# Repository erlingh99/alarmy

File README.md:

# Alarmy

A sunrise alarm system with a web interface and Raspberry Pi Pico W based light control. Wake up naturally with a simulated sunrise.

## Project Overview

This project consists of three main components:

- **Frontend**: React-based web interface for managing alarms
- **Backend**: FastAPI server for alarm storage and management 
- **Embedded**: Raspberry Pi Pico W controller for LED and buzzer control in 100% heapless Rust

## Quick Start

### Backend & Frontend

```bash
# Start the complete system using Docker
docker compose up -d --build
```

The web interface will be available at localhost port 80

### Pico W Setup

1. Flash the firmware following instructions in `/embedded/README.md`
2. Wire up a breadboard or use the PCB
3. Power up the device

## Development

See the individual component READMEs for detailed development instructions:

- [Frontend Documentation](frontend/README.md)
- [Backend Documentation](backend/README.md)
- [Embedded Documentation](embedded/README.md)

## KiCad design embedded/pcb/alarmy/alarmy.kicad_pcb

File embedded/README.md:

# Raspberry Pi Pico W Alarm Controller

This is the embedded component of the alarm project, implemented in Rust using the Embassy async runtime. It controls a PWM-capable LED strip and optional buzzer, fetching alarm schedules from the backend.

## Provisioning a device

The CYW43 WiFi chip blobs and the WiFi credentials are not part of the firmware binary. They are
flashed once per device at fixed addresses (see `memory_layout.toml`), so the firmware served
publicly for OTA contains no secrets. All scripts use picotool and need the Pico in BOOTSEL mode.

A new device, from `embedded/`:

```bash
uv run scripts/flash_blobs.py --no-reboot          # CYW43 blobs + credentials (prompts for SSID and password)
uv run scripts/flash_bootloader.py --no-reboot     # builds and flashes the bootloader
uv run scripts/flash_firmware.py                   # builds and flashes the firmware, then reboots
```

After that the firmware updates itself over OTA. Other useful variants:

```bash
uv run scripts/flash_blobs.py --only creds --ssid MyNetwork   # change network
uv run scripts/flash_blobs.py --only cyw43                    # chip blobs only
uv run scripts/flash_firmware.py --no-build                   # flash the existing release ELF
```

Without credentials the firmware boots but logs `No usable WiFi credentials in flash` over USB
serial every minute.

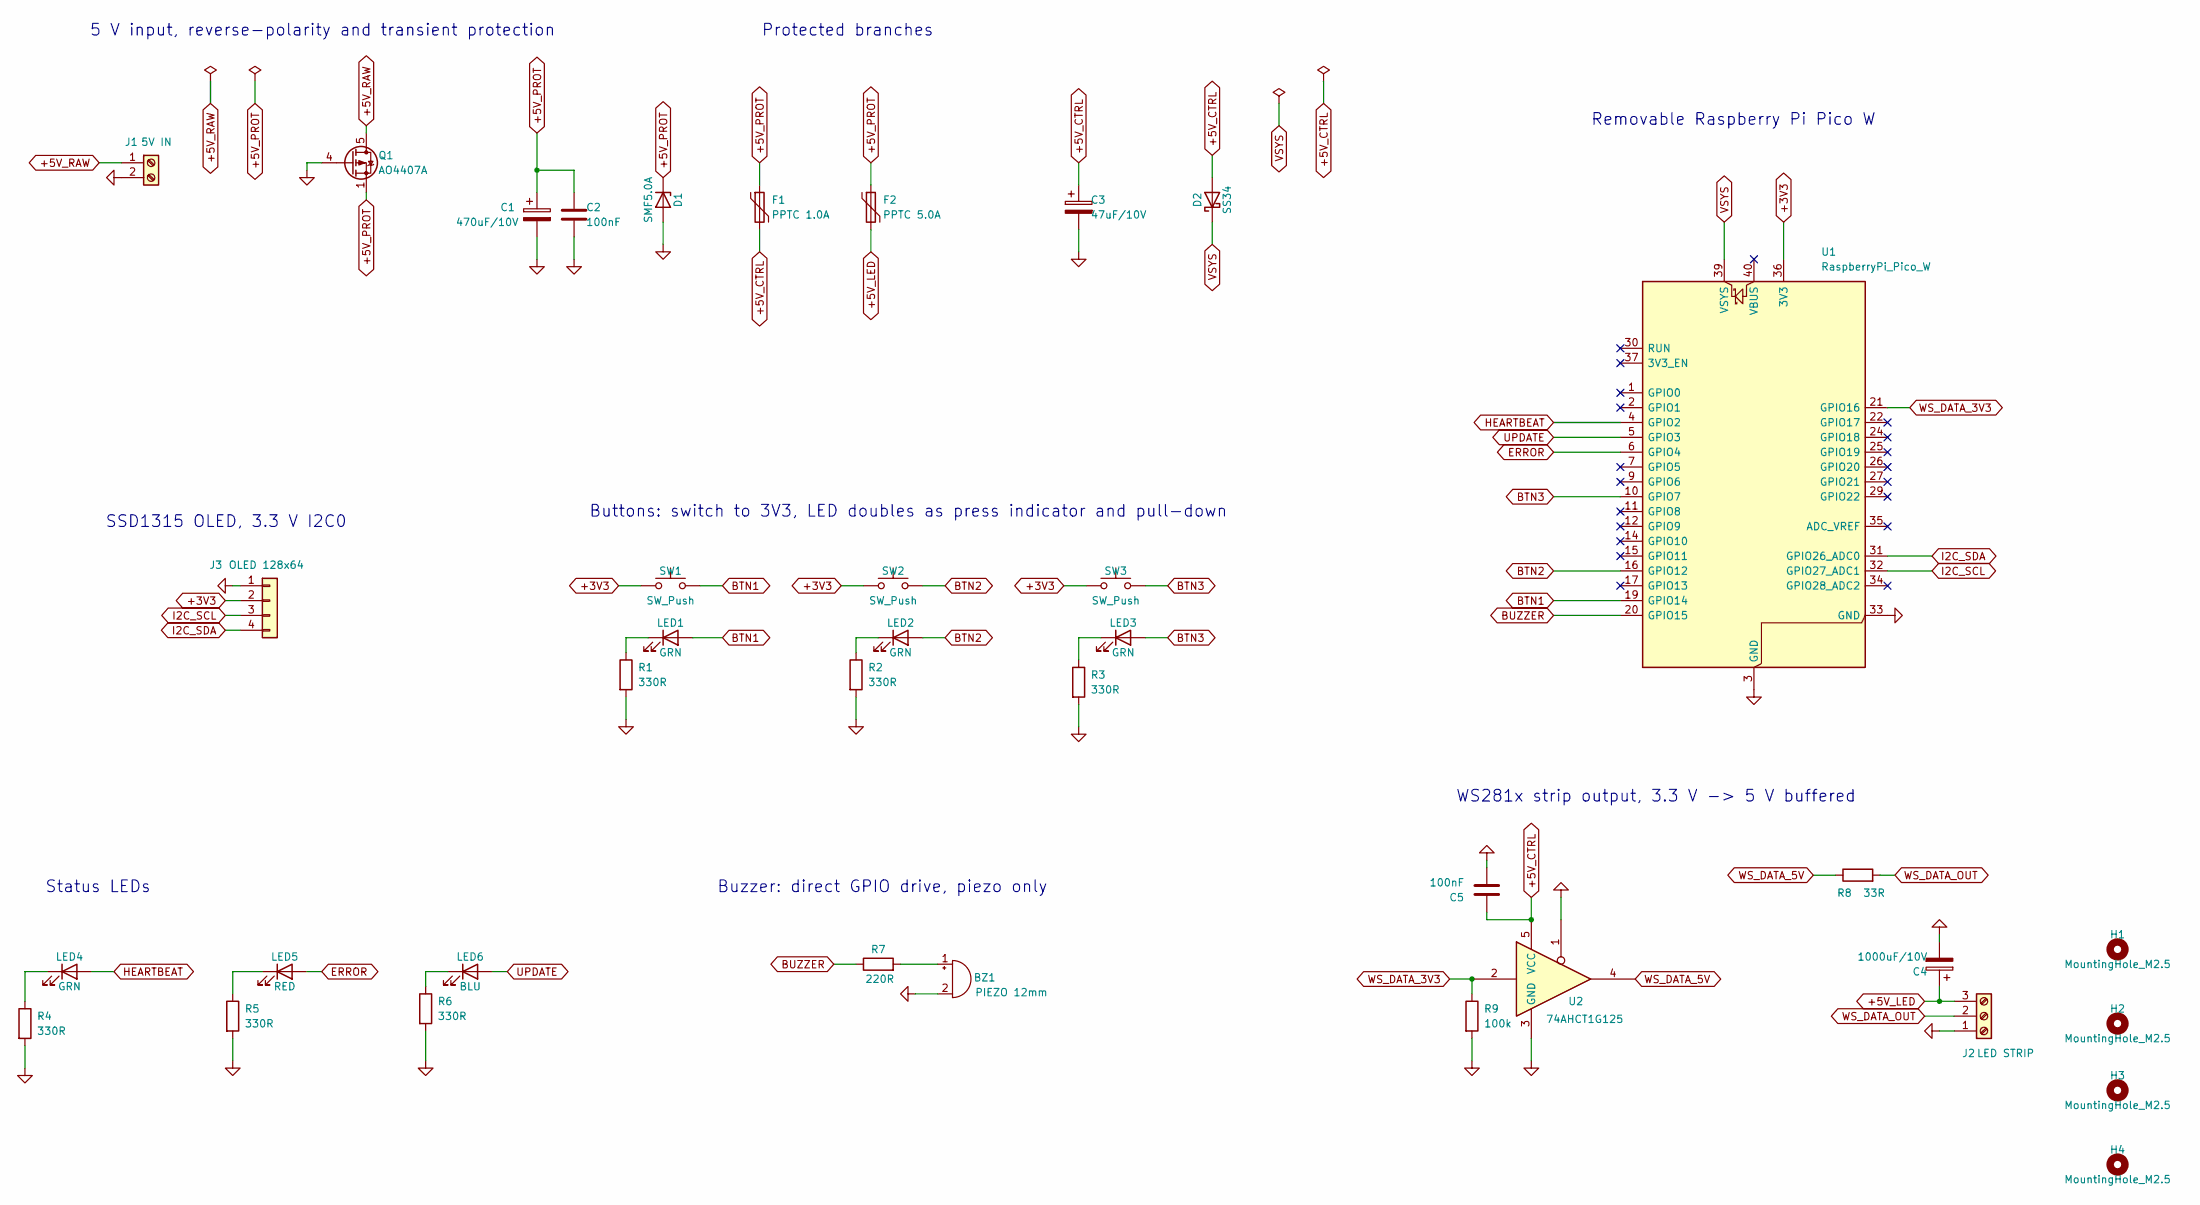
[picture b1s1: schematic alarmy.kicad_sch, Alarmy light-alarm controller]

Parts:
BZ1: PIEZO 12mm; Buzzer_12x9.5RM7.6
C1: 470uF/10V; CP_Radial_D8.0mm_P3.50mm
C2, C5: 100nF; C_Disc_D5.0mm_W2.5mm_P5.00mm
C3: 47uF/10V; CP_Radial_D5.0mm_P2.50mm
C4: 1000uF/10V; CP_Radial_D12.5mm_P5.00mm
D1: SMF5.0A; D_SMF; MPN SMF5.0A
D2: SS34; D_SMA; MPN SS34
F1: PPTC 1.0A; PPTC_Radial_P5.08mm; MPN MF-MSMF110-2
F2: PPTC 5.0A; PPTC_Radial_P10.0mm; MPN PTR030V0500-BK
H1, H2, H3, H4: MountingHole_M2.5; MountingHole_2.7mm_M2.5
J1: 5V IN; TerminalBlock_Phoenix_MKDS-1,5-2-5.08_1x02_P5.08mm_Horizont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; MPN Phoenix MKDS 1,5/2-5,08
J2: LED STRIP; TerminalBlock_Phoenix_MKDS-1,5-3-5.08_1x03_P5.08mm_Horizont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; MPN Phoenix MKDS 1,5/3-5,08
J3: OLED 128x64; OLED_SSD1315_0.96in_I2C
LED1, LED2, LED3, LED4: GRN; LED_D5.0mm
LED5: RED; LED_D5.0mm
LED6: BLU; LED_D5.0mm
Q1: AO4407A; SOIC-8_3.9x4.9mm_P1.27mm; MPN AO4407A
R1, R2, R3, R4, R5, R6: 330R; R_Axial_DIN0207_L6.3mm_D2.5mm_P7.62mm_Horizontal
R7: 220R; R_Axial_DIN0207_L6.3mm_D2.5mm_P7.62mm_Horizontal
R8: 33R; R_Axial_DIN0207_L6.3mm_D2.5mm_P7.62mm_Horizontal
R9: 100k; R_Axial_DIN0207_L6.3mm_D2.5mm_P7.62mm_Horizontal
SW1, SW2, SW3: SW_Push; SW_PUSH_6mm
U1: RaspberryPi_Pico_W; RaspberryPi_Pico_Common_THT
U2: 74AHCT1G125; SOT-23-5; MPN SN74AHCT1G125DBVR

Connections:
+3V3: J3.2, SW1.1, SW2.1, SW3.1, U1.36 (3V3)
+5V_CTRL: C3.1, C5.1, D2.2 (A), F1.2, U2.5 (VCC)
+5V_LED: C4.1, F2.2, J2.3
+5V_PROT: C1.1, C2.1, D1.1 (K), F1.1, F2.1, Q1.1 (S), Q1.2 (S), Q1.3 (S)
+5V_RAW: J1.1, Q1.5 (D), Q1.6 (D), Q1.7 (D), Q1.8 (D)
BTN1: LED1.2 (A), SW1.2, U1.19 (GPIO14)
BTN2: LED2.2 (A), SW2.2, U1.16 (GPIO12)
BTN3: LED3.2 (A), SW3.2, U1.10 (GPIO7)
BUZZER: R7.1, U1.20 (GPIO15)
ERROR: LED5.2 (A), U1.6 (GPIO4)
GND: BZ1.2 (-), C1.2, C2.2, C3.2, C4.2, C5.2, D1.2 (A), J1.2, J2.1, J3.1, Q1.4 (G), R1.2, R2.2, R3.2, R4.2, R5.2, R6.2, R9.2, U1.3 (GND), U1.8 (GND), U1.13 (GND), U1.18 (GND), U1.23 (GND), U1.28 (GND), U1.33 (GND), U1.38 (GND), U2.1, U2.3 (GND)
HEARTBEAT: LED4.2 (A), U1.4 (GPIO2)
I2C_SCL: J3.3, U1.32 (GPIO27_ADC1)
I2C_SDA: J3.4, U1.31 (GPIO26_ADC0)
unnamed: BZ1.1 (+), R7.2
unnamed: LED1.1 (K), R1.1
unnamed: LED2.1 (K), R2.1
unnamed: LED3.1 (K), R3.1
unnamed: LED4.1 (K), R4.1
unnamed: LED5.1 (K), R5.1
unnamed: LED6.1 (K), R6.1
UPDATE: LED6.2 (A), U1.5 (GPIO3)
VSYS: D2.1 (K), U1.39 (VSYS)
WS_DATA_3V3: R9.1, U1.21 (GPIO16), U2.2
WS_DATA_5V: R8.1, U2.4
WS_DATA_OUT: J2.2, R8.2

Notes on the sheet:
Protected branches
Buzzer: direct GPIO drive, piezo only
5 V input, reverse-polarity and transient protection
WS281x strip output, 3.3 V -> 5 V buffered
SSD1315 OLED, 3.3 V I2C0
Status LEDs
Buttons: switch to 3V3, LED doubles as press indicator and pull-down
Removable Raspberry Pi Pico W

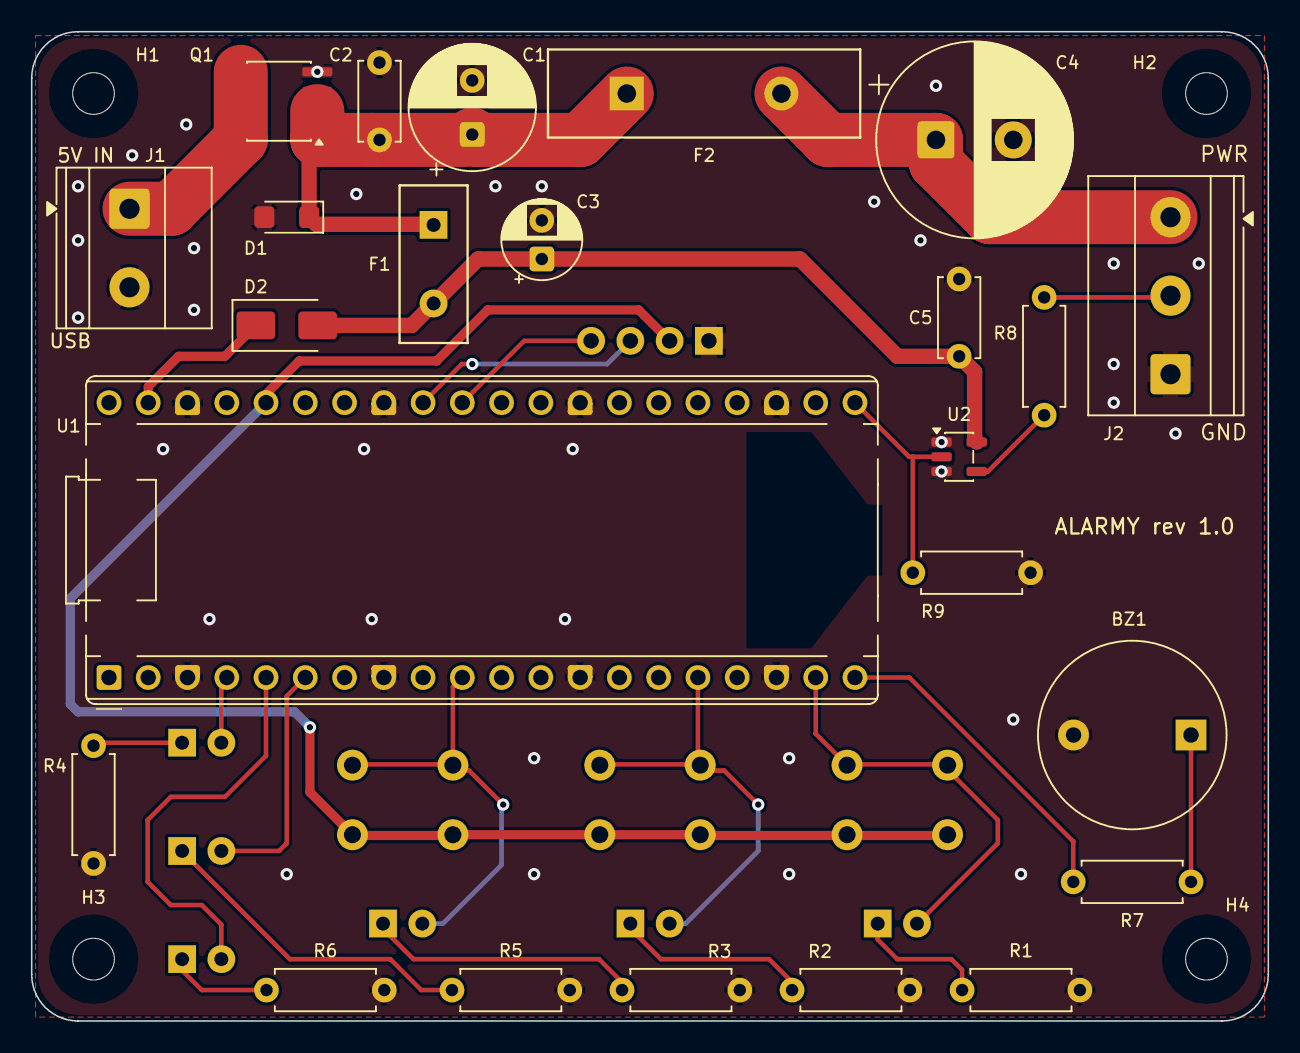
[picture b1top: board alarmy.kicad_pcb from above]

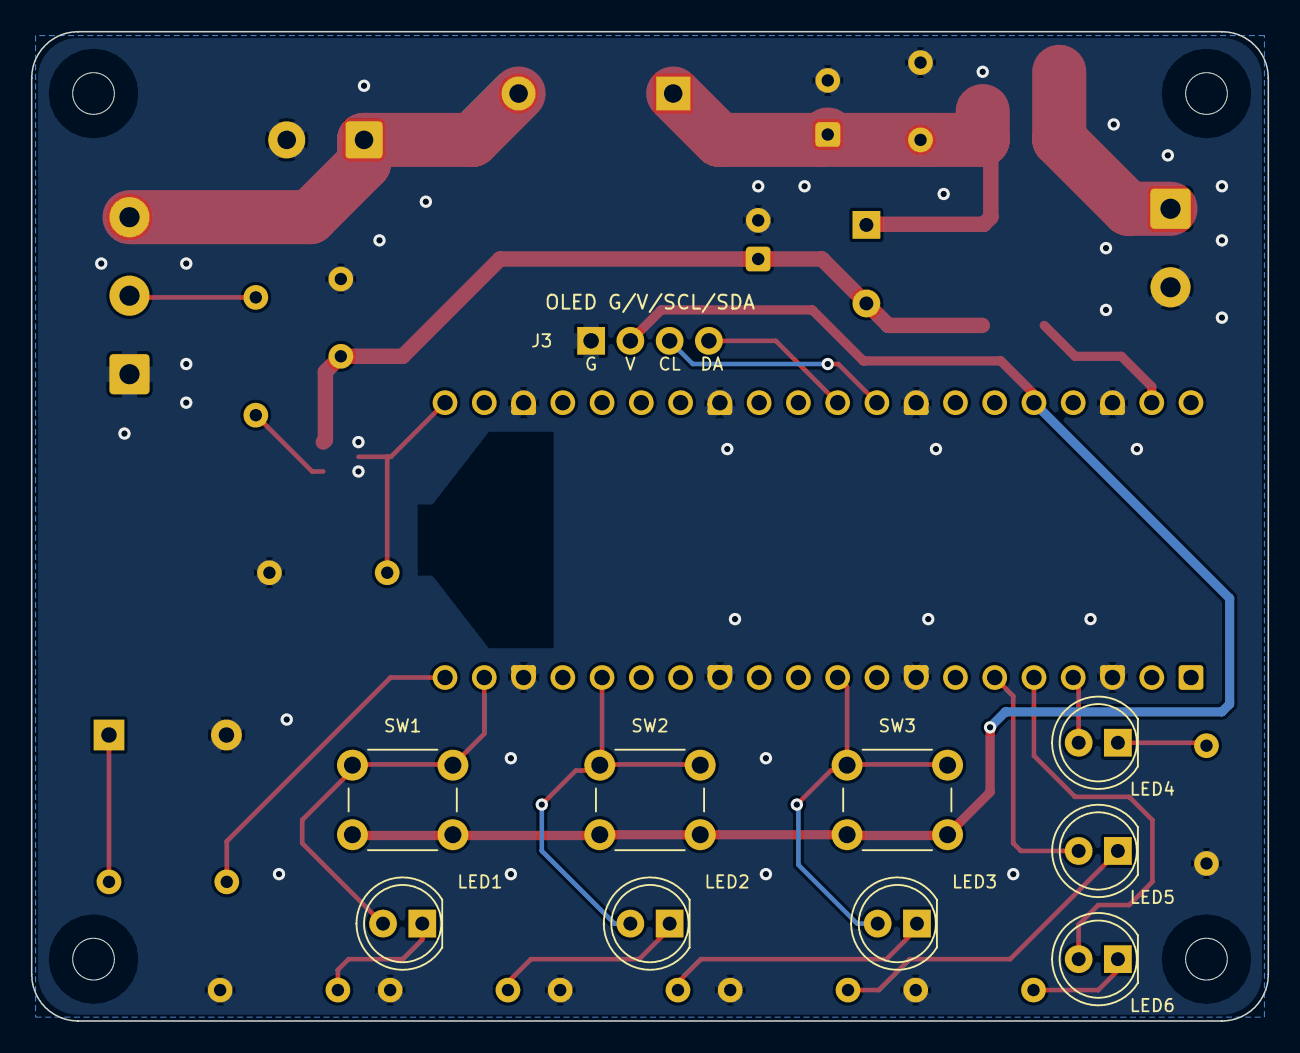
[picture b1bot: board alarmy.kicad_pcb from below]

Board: 2 copper layers, 80.0 x 64.0 mm, 38 parts (10 on the bottom side), 26 nets.
